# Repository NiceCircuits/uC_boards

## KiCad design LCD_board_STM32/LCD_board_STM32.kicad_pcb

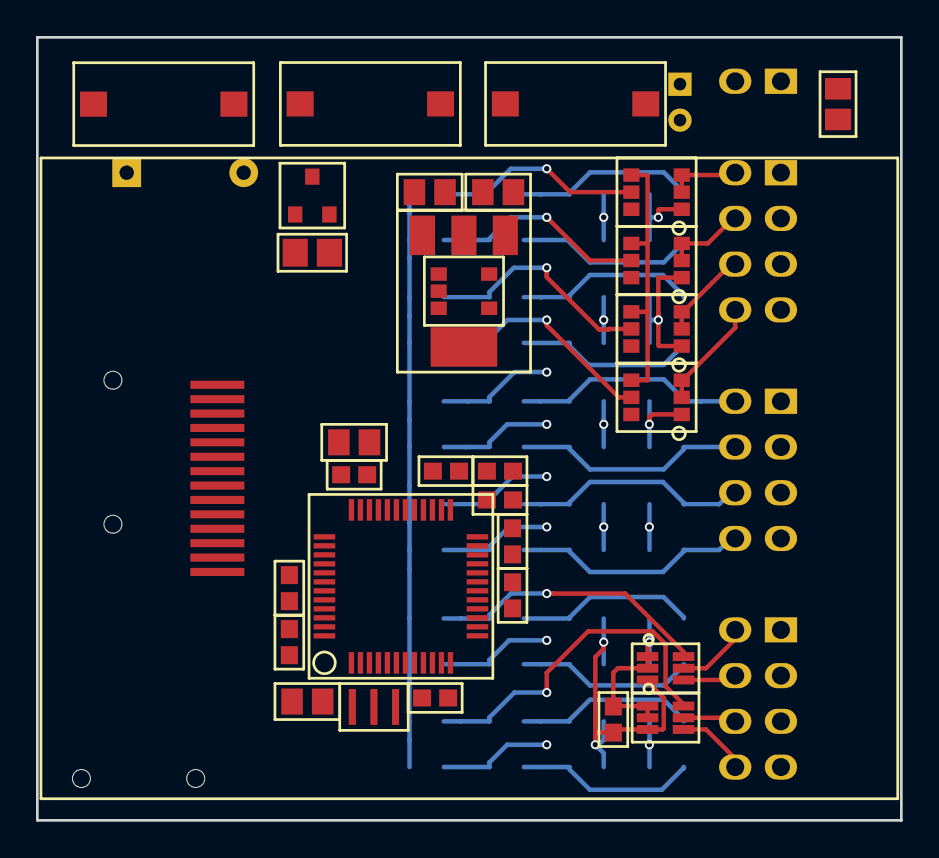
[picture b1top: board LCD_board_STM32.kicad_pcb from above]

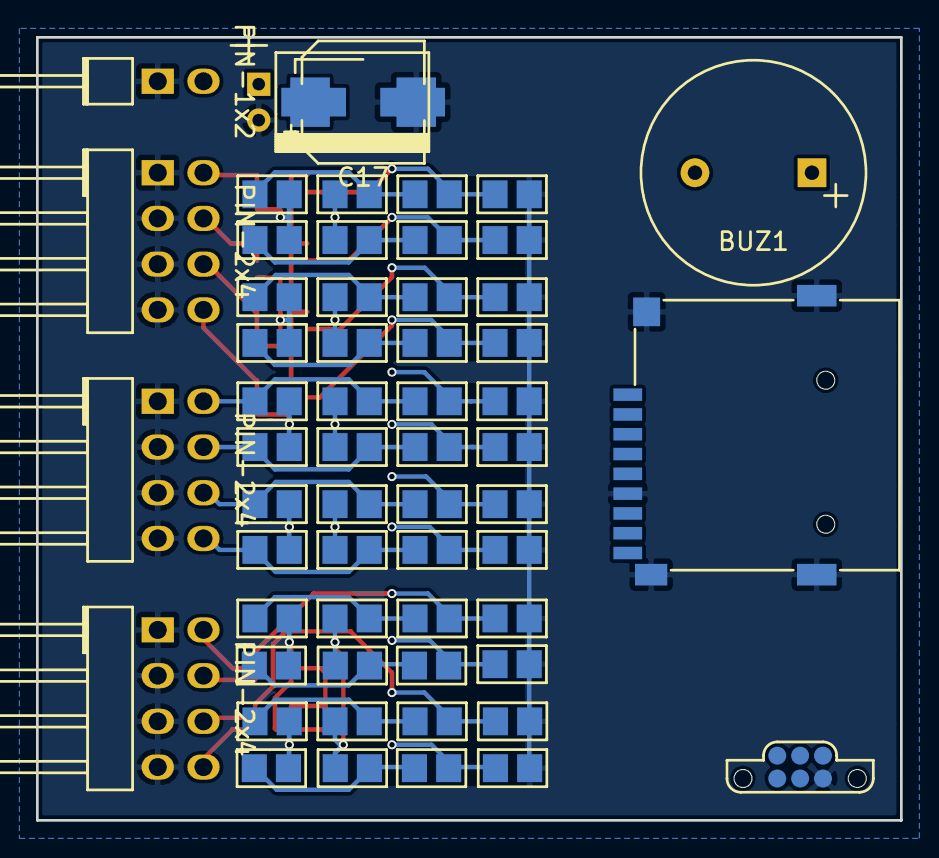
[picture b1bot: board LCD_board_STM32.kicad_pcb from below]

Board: 2 copper layers, 48.0 x 43.5 mm, 89 parts (58 on the bottom side), 44 nets.

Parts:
BUZ1: PIN-1x2; buzzer_12x5.5
C1, C2, C3, C4, C5, C6, C7, C8, C11, C12, C13, C14: C; 0805_M
C9, C19, C20, C21, C22: 100n; 0603_N
C15: Cpol; Tantal_X_M
C16: Cpol; Cpol_5.0_7.0_HR_N
C17: Cpol; Cpol-6.3x7.7
C18, C23, C24, C25: C; 0805_N
C26: C; 0603_N
CON1, CON2, CON3: PIN-2x4; PIN-2x4_angled_N
CON4: SWD-6pin; pogo_clip_6
CON5: PIN-1x2; PIN-2x1_angled_N
CON6: micro_sd; micro_sd_MCSP-Q-08-A-SG
D1: diode_LED; 0805_N
Q1: PDTC114ET; SOT23-3_N
Q2: CSTCE; XTAL_CSTCE
Q3, Q4, Q5, Q6: FDC6331L; SOT23-6_N
R1, R2, R3, R4, R5, R6, R7, R8, R9, R10, R11, R12, R13, R14, R15, R16, R17, R18, R19, R20, R21, R22, R23, R24, R25, R26, R27, R28, R29, R30, R31, R32, R33, R34, R35, R36, R37: R; 0805_R_M
R38, R39, R40, R41: R; 0603_R_N
SW1, SW2, SW3: MicroswitchSmt6x4_V; MicroswitchSmd6x4_N
U1: STM32_LQFP48; ST_LQFP48_ST_default
U2: TFT_1_8_ST7735; TFT_1_8_ST7735_N
U3, U4: NCS199A1; SC70-6_M
U5: AMS1117-3.3; SOT223_N
U6: LP2980AIM5-3.0; SOT23-5_N

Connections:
GND: C1.2, C2.2, C3.2, C4.2, C5.2, C6.2, C7.2, C8.2, C9.2, C11.2, C12.2, C13.2, C14.2, C15.2, C16.2, C17.2, C18.2, C19.2, C20.2, C21.2, C22.2, C23.2, C24.2, C25.2, C26.2, CON1.1, CON1.3, CON1.5, CON1.7, CON2.1, CON2.3, CON2.5, CON2.7, CON3.1, CON3.3, CON3.5, CON3.7, CON4.5, CON5.1, CON6.0, CON6.6, D1.1, Q1.2, Q2.2, Q3.1, Q4.1, Q5.1, Q6.1, R17.1, R18.1, R19.1, R20.1, R21.1, R22.1, R23.1, R24.1, R33.1, R34.1, R35.1, R36.1, R38.1, SW1.1, SW2.1, SW3.1, U1.8, U1.23, U1.35, U1.47, U3.1, U3.2, U4.1, U4.2, U5.1, U6.2
MOSI: U1.41, U2.8
unnamed: BUZ1.1, R37.1
unnamed: BUZ1.2, Q1.3
unnamed: C26.1, R39.1, R41.1, U1.25
unnamed: D1.2, R41.2
unnamed: Q2.1, U1.6
unnamed: Q2.3, U1.5
unnamed: R38.2, U1.44
unnamed: R40.2, U1.17
PIN0: C11.1, CON1.2, Q3.2, Q3.3, R25.1, R29.2
PIN1: C12.1, CON1.4, Q4.2, Q4.3, R26.1, R30.2
PIN2: C13.1, CON1.6, Q5.2, Q5.3, R27.1, R31.2
PIN3: C14.1, CON1.8, Q6.2, Q6.3, R28.1, R32.2
PIN4: C1.1, CON2.2, R1.1, R5.2
PIN5: C2.1, CON2.4, R2.1, R4.2
PIN6: C3.1, CON2.6, R3.1, R6.2
PIN7: C4.1, CON2.8, R7.1, R10.2
PIN8: C5.1, CON3.2, R8.1, R11.2, U3.5
PIN9: C6.1, CON3.4, R9.1, R12.2, U3.4
PIN10: C7.1, CON3.6, R13.1, R15.2, U4.5
PIN11: C8.1, CON3.8, R14.1, R16.2, U4.4
RST: CON4.3, U1.7
SW1: SW1.2, U1.10
SW2: SW2.2, U1.38
SW3: SW3.2, U1.20
SWCLK: CON4.4, U1.37
SWDIO: CON4.2, U1.34
SWO/SCK: CON4.6, U1.39, U2.9
TFT_CS: U1.2, U2.12
VCC: C9.1, C19.1, C20.1, C21.1, C22.1, C23.1, C24.1, C25.1, CON4.1, CON6.4, R1.2, R2.2, R3.2, R7.2, R8.2, R9.2, R13.2, R14.2, R25.2, R26.2, R27.2, R28.2, R39.2, U1.1, U1.9, U1.24, U1.36, U1.48, U3.3, U4.3, U5.2, U6.5
VPP: C15.1, C16.1, C17.1, C18.1, CON5.2, Q3.4, Q4.4, Q5.4, Q6.4, R37.2, U5.3, U6.1, U6.3
uC0: Q3.5, R29.1, R33.2, U1.18
uC1: Q4.5, R30.1, R34.2, U1.19
uC2: Q5.5, R31.1, R35.2, U1.45
uC3: Q6.5, R32.1, R36.2, U1.21
uC4: R5.1, R17.2, U1.46
uC5: R4.1, R18.2, U1.11
uC6: R6.1, R19.2, U1.12
uC7: R10.1, R20.2, U1.13
uC8: R11.1, R21.2, U1.14, U3.6
uC9: R12.1, R22.2, U1.15
uC10: R15.1, R23.2, U1.16, U4.6
uC11: R16.1, R24.2, R40.1

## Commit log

2016-11-07 Working on circuit.
2016-11-07 Rename nets
